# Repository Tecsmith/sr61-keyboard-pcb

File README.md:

# SR61 - MicroMod 60% Custom Keyboard PCB

[![CC-0 license](https://shields.io/badge/-BY--SA_4.0-black?logo=creativecommons&logoColor=%23000&labelColor=%23c1c1c1
)](https://creativecommons.org/licenses/by-sa/4.0/)

***Featuring SparkFun's MicroMod Processor Boards***

---

> [PCBWay](https://pcbway.com) had gratefully sponsored the production of the first 5 RevA PCBs, and a partial assembly service.
>
> 
>
> Thank you [PCBWay](https://pcbway.com/)!

Please follow the updates to this production process on the [changelog](CHANGELOG.md) page.

---

Published as Open Source, under a [ Creative Commons Share-alike 4.0 International](LICENSE.md).

### **Rev C** &nbsp; 

> ~~&#128077; **WORKING, OK TO BUILD**~~ &nbsp; 

* [PDF Schematic](docs/sr61-revC.pdf)
* [EAGLE PCB](EAGLE/sr61/sr61-revC.brd)
* [EAGLE Schematic](EAGLE/sr61/sr61-revC.sch)

* Notes:
    - Keymap Working on both STM32 and PR2040
    - *(Optional EEPROM not tested yet)*

### QMK code:

* https://github.com/Tecsmith/sr61-keyboard-qmk
* USB Identifier registered with [pid.codes](https://pid.codes/) = [`1209`/`7672`](https://pid.codes/1209/7672/)

### Layout

* [KLE JSON](./kle/sr61-micromod-poker.json)

*****

## Features

**SR61-MicroMod** - using SparkFun MicroMod STM32 or RP2040 M.2 module

### Core Design Elements

- 60% form factor
    - Design to be compatible with GH60/HK60 cases
    - Also compatible with Anne Pro 2 cases *(~~drop in~~ QMK replacement for existing AP2's or AP2 cases)* *[Removal of battery and minor case cut in the battery compartment required.]*
    - MicroMod positioned in case *"battery compartment"* space.

- QMK + VIA default f/w
    - Wired only *(no wireless)*
    - Default key-maps for Mac users

- User choice of microcontroller
    
    - [STM32 Processor](https://www.sparkfun.com/products/17713) 
        - ARM Cortex-M4, 168MHz, 1MB Flash, 192kB SRAM
        - https://github.com/Tecsmith/sr61-keyboard-qmk

    - [RP2040 Processor](https://www.sparkfun.com/products/17720) 
        - ARM Cortex-M0+, 133MHz, 128Mb Flash (16MB external), 264kB SRAM in six banks
        
- USB-C *(left side)*

    ... but also optional JST connector for [ai03 Unified C3 Daughterboard](https://github.com/ai03-2725/Unified-Daughterboard)

- ESD, Over Voltage and Over Current protection

    ... and cable shield noise filter

- Hot-swap, 5 pin switch slots

- PCB mounted stabs compatibility

- Dual ANSI / ISO layout support

- 61-Key (ANSI) / 62-Key (ISO) Layout [1.25, 1.25, 1.25, **6.25**, 1.25, 1.25, 1.25, 1.25] bottom row *(a.k.a. "Poker" / "POK3R" Layout)*

- Limited RGB LEDs *(SK6812 mini-E)*

    - RGB Caps Lock Indicator

    - North facing RGB's under the `5`, `6`, `7` & `8` keys for layer indicator

    - WS2812/SK6812 breakout for optional external LEDs

- Spare GPIO pins (`52` & `63`) breakout for expansion

   ... e.g., ~~add speaker~~

- Both `[Reset]` and `[Boot]` buttons *(as per MicroMod ref. design)*

    ... plus under space-bar Boot pins for bootload without disassembly *(press while inserting cable for bootloader function)*

---

Made with :heart: by Silvino R.

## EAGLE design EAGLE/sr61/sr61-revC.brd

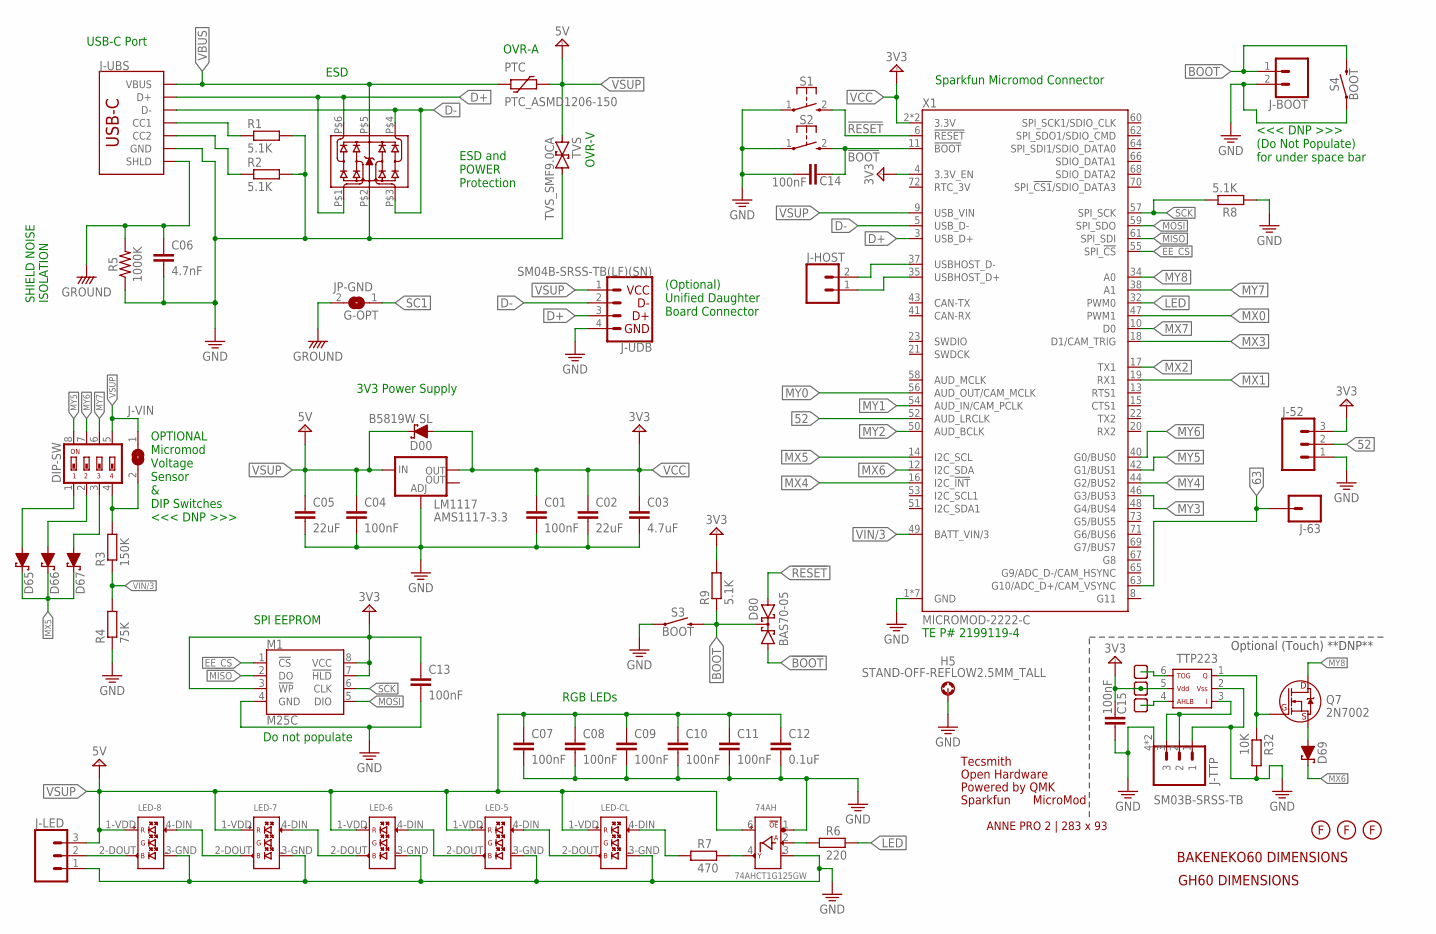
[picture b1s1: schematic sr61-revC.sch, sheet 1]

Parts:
74AH: 74AHCT1G125GW; SC-88A__TSSOP5__SOT353-1
C01, C04: 100nF; 0603
C02, C05: 22uF; 0603
C03: 4.7uF; 0603
C06: 4.7nF; 0603
C07, C08, C09, C10, C11, C13, C14, C15: 100nF; C0603
C12: 0.1uF; C0603
D00: B5819W SL; SOD-123
D65, D66, D67, D69: 1N5819WS; SOD-123
D80: BAS70-05; SOT23
DIP-SW: DIP004; DIP-1.27-004
ESD: ESD_SRV05-4; SOT-23-6L
FP_AP2: FOOTPRINT-AP2
H5: STAND-OFF-REFLOW2.5MM_TALL; STAND-OFF-REFLOW-M2.5
J-52: CONN_03; 1X03
J-63: CONN_01; 1X01
J-BOOT: CONN_02; 1X02
J-HOST: CONN_02; 1X02
J-LED: CONN_03; 1X03
J-TTP: SM03B-SRSS-TB; CONN_SM03B-SRSS-TB_JST
J-UBS: USB_C_2-LAYER; USB-C-16P
J-UDB: SM04B-SRSS-TB(LF)(SN); 1X04_1MM_RA
J-VIN: JUMPER-1X2; SOLDERJUMPER_ARROW_NOPASTE
JP-GND: G-OPT; SOLDERJUMPER_ARROW_NOPASTE
LED-5, LED-6, LED-7, LED-8: SK6812-E-REVERSE; SK6812-E-MILL
LED-CL: SK6812-E-REVERSE; SK6812-E-MILL
LM1117: AMS1117-3.3; SOT223
LOGO1: OSHW-LOGOL; OSHW-LOGO-L
M1: M25C; 8-SOIC
PTC: PTC_ASMD1206-150; SMD_PTC
Q7: 2N7002; SOT23-3
R1, R2, R8, R9: 5.1K; R0603
R3: 150K; R0603
R4: 75K; R0603
R5: 1000K; 0603
R6: 220; R0603
R7: 470; R0603
R32: 10K; R0603
S1, S2: MOMENTARY-SWITCH-SPST-1; SKRKAEE020
S3, S4: BOOT; TACTILE_SWITCH_SMD_5.2MM
TP1, TP2, TP3: TEST-POINT.3SQ; PAD.03X.03-SQ
TTP223: TTP223-BA6; TTP223B
TVS: TVS_SMF9.0CA; SOD123FL-BI
U$3: MICROMOD-LOGO
U$5: SPARKFUN_LOGO0.2; SFE_LOGO_NAME_FLAME_.2
U$6: QMK_LOGO
U$8: TECSMITH-LOGOLONG; TECSMITH-NAME
U$20, U$21, U$22: FIDUCIAL
U$24: FOOTPRINT-BAKENEKO60
U$27: FOOTPRINT-DIMS-GH60
X1: MICROMOD-2222-C; M.2-CONNECTOR-E

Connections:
52: J-52.2, X1.52 (AUD_LRCLK)
63: J-63.1, X1.63 (G10/ADC_D+/CAM_VSYNC)
!BOOT: C14.1, D80.1 (A1), S2.2 (3), X1.11 (!BOOT!)
!RESET: D80.2 (A2), S1.2 (3), X1.6 (!RESET!)
BOOT: D80.3 (C), J-BOOT.1, R9.1, S3.3 (2), S3.4 (2), S4.3 (2), S4.4 (2)
CC1: J-UBS.A5 (CC1), R1.1
CC2: J-UBS.B5 (CC2), R2.1
D+: ESD.P$1, ESD.P$6, J-UBS.A6 (D+), J-UBS.B6 (D+), J-UDB.3 (D+), X1.3 (USB_D+)
D-: ESD.P$3, ESD.P$4, J-UBS.A7 (D-), J-UBS.B7 (D-), J-UDB.2 (D-), X1.5 (USB_D-)
EE_CS: M1.1 (!CS), X1.55 (SPI_!CS!)
GND: 74AH.1 (!OE), 74AH.3 (3_GND), C01.2, C02.2, C03.2, C04.2, C05.2, C06.2, C07.2, C08.2, C09.2, C10.2, C11.2, C12.2, C13.2, C14.2, C15.2, ESD.P$2, H5.1, J-52.1, J-BOOT.2, J-LED.1, J-TTP.1, J-TTP.4 (M), J-TTP.5 (M), J-UBS.GND, J-UBS.GND2 (GND), J-UDB.4 (GND), LED-5.3-GND (3_GND), LED-6.3-GND (3_GND), LED-7.3-GND (3_GND), LED-8.3-GND (3_GND), LED-CL.3-GND (3_GND), LM1117.1 (ADJ), M1.4 (GND), R1.2, R2.2, R4.1, R5.1, R8.1, R32.2, S1.1, S2.1, S3.1, S3.2 (1), S4.1, S4.2 (1), TTP223.2, TVS.P$2 (2), X1.1 (GND), X1.7 (GND), X1.33 (GND), X1.36 (GND), X1.39 (GND), X1.45 (GND), X1.75 (GND)
GROUND: C06.1, J-UBS.SHLD1 (SHLD), J-UBS.SHLD2 (SHLD), J-UBS.SHLD3 (SHLD), J-UBS.SHLD4 (SHLD), J-UBS.SHLD5 (SHLD), J-UBS.SHLD6 (SHLD), J-UBS.SHLD7 (SHLD), J-UBS.SHLD8 (SHLD), JP-GND.2, R5.2
LED: R6.2, X1.32 (PWM0)
LED1ST: 74AH.2 (A_DIN), R6.1
MISO: M1.2 (DO), X1.61 (SPI_SDI)
MOSI: M1.5 (DIO), X1.59 (SPI_SDO)
MX0: X1.47 (PWM1); also elsewhere on the board
MX1: X1.19 (RX1); also elsewhere on the board
MX2: X1.17 (TX1); also elsewhere on the board
MX3: X1.18 (D1/CAM_TRIG); also elsewhere on the board
MX4: X1.16 (I2C_!INT!); also elsewhere on the board
MX5: D65.C, D66.C, D67.C, X1.14 (I2C_SCL); also elsewhere on the board
MX6: D69.C, X1.12 (I2C_SDA); also elsewhere on the board
MX7: X1.10 (D0); also elsewhere on the board
MY0: X1.56 (AUD_OUT/CAM_MCLK); also elsewhere on the board
MY1: X1.54 (AUD_IN/CAM_PCLK); also elsewhere on the board
MY2: X1.50 (AUD_BCLK); also elsewhere on the board
MY3: X1.46 (G3/BUS3); also elsewhere on the board
MY4: X1.44 (G2/BUS2); also elsewhere on the board
MY5: DIP-SW.8, X1.42 (G1/BUS1); also elsewhere on the board
MY6: DIP-SW.7, X1.40 (G0/BUS0); also elsewhere on the board
MY7: DIP-SW.6, X1.38 (A1); also elsewhere on the board
MY8: Q7.3 (D), X1.34 (A0); also elsewhere on the board
unnamed: LED-5.4-DIN (4_DIN), LED-CL.2-DOUT (2_DOUT)
unnamed: LED-5.2-DOUT (2_DOUT), LED-6.4-DIN (4_DIN)
unnamed: LED-6.2-DOUT (2_DOUT), LED-7.4-DIN (4_DIN)
unnamed: LED-7.2-DOUT (2_DOUT), LED-8.4-DIN (4_DIN)
unnamed: 74AH.4 (Y_DOUT), R7.2
unnamed: LED-CL.4-DIN (4_DIN), R7.1
unnamed: TP1.1, TTP223.6
unnamed: J-LED.2, LED-8.2-DOUT (2_DOUT)
unnamed: D65.A, DIP-SW.1
unnamed: DIP-SW.4, J-VIN.2, R3.2
unnamed: D66.A, DIP-SW.2
unnamed: D67.A, DIP-SW.3
unnamed: TP3.1, TTP223.4
unnamed: D69.A, Q7.2 (S)
unnamed: Q7.1 (G), R32.1, TTP223.1
unnamed: J-TTP.2, J-TTP.3, TTP223.3
SC1: JP-GND.1
SCK: M1.6 (CLK), R8.2, X1.57 (SPI_SCK)
USBHOST_D+: J-HOST.1, X1.35 (USBHOST_D+)
USBHOST_D-: J-HOST.2, X1.37 (USBHOST_D-)
VBUS: ESD.P$5, J-UBS.VBUS1 (VBUS), J-UBS.VBUS2 (VBUS), PTC.P$1 (1)
VCC: C01.1, C02.1, C03.1, C13.1, C15.1, D00.A, J-52.3, LM1117.2 (OUT), M1.3 (!WP), M1.7 (!HLD), M1.8 (VCC), R9.2, TP2.1, TTP223.5, X1.2 (3.3V), X1.4 (3.3V_EN), X1.74 (3.3V)
VIN/3: R3.1, R4.2, X1.49 (BATT_VIN/3)
VSUP: 74AH.6 (5_VCC), C04.1, C05.1, C07.1, C08.1, C09.1, C10.1, C11.1, C12.1, D00.C, DIP-SW.5, J-LED.3, J-UDB.1 (VCC), J-VIN.1, LED-5.1-VDD (1_VDD), LED-6.1-VDD (1_VDD), LED-7.1-VDD (1_VDD), LED-8.1-VDD (1_VDD), LED-CL.1-VDD (1_VDD), LM1117.3 (IN), PTC.P$2 (2), TVS.P$1 (1), X1.9 (USB_VIN)

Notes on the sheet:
ESD
OVR-A
OVR-V
USB-C Port
ESD and POWER Protection
OPTIONAL Micromod Voltage Sensor & DIP Switches <<< DNP >>>
(Optional) Unified Daughter Board Connector
Sparkfun Micromod Connector
3V3 Power Supply
RGB LEDs
SHIELD NOISE ISOLATION
SPI EEPROM
TE P# 2199119-4
<<< DNP >>> (Do Not Populate) for under space bar
Do not populate
Optional (Touch) **DNP**

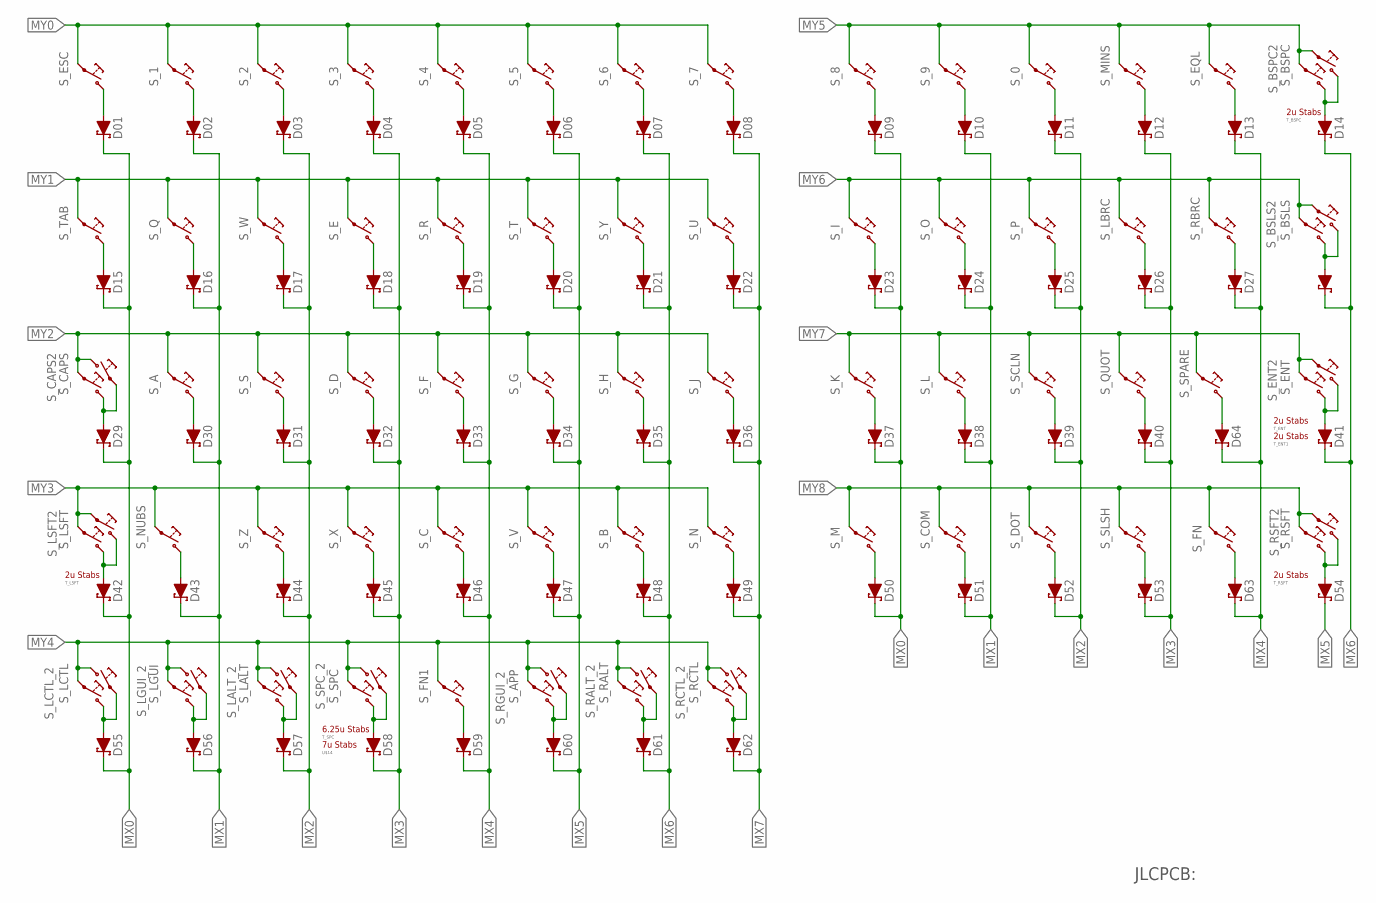
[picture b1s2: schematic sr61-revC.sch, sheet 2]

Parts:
D01, D02, D03, D04, D05, D06, D07, D08, D09, D10, D11, D12, D13, D14, D15, D16, D17, D18, D19, D20, D21, D22, D23, D24, D25, D26, D27, D28, D29, D30, D31, D32, D33, D34, D35, D36, D37, D38, D39, D40, D41, D42, D43, D44, D45, D46, D47, D48, D49, D50, D51, D52, D53, D54, D55, D56, D57, D58, D59, D60, D61, D62, D63, D64: 1N5819WS; SOD-123
S_0, S_1, S_2, S_3, S_4, S_5, S_6, S_7, S_8, S_9: MX-5-PIN-HOTSWAP-VIA
S_A: MX-5-PIN-HOTSWAP-VIA
S_APP: MX-5-PIN-HOTSWAP-VIA
S_B: MX-5-PIN-HOTSWAP-VIA
S_BSLS: MX-5-PIN-HOTSWAP-VIA
S_BSLS2: MX-5-PIN-HOTSWAP-VIANO-SILK; MX-5-PIN-HOTSWAP-VIA-NS
S_BSPC: MX-5-PIN-HOTSWAP-VIA
S_BSPC2: MX-5-PIN-HOTSWAP-VIANO-SILK; MX-5-PIN-HOTSWAP-VIA-NS
S_C: MX-5-PIN-HOTSWAP-VIA
S_CAPS: MX-5-PIN-HOTSWAP-VIA
S_CAPS2: MX-5-PIN-MILMAX-3305-XNO-SILK; MX-5-PIN-MILMAX-3305-X-NS
S_COM: MX-5-PIN-HOTSWAP-VIA
S_D: MX-5-PIN-HOTSWAP-VIA
S_DOT: MX-5-PIN-HOTSWAP-VIA
S_E: MX-5-PIN-HOTSWAP-VIA
S_ENT: MX-5-PIN-HOTSWAP-VIA
S_ENT2: MX-5-PIN-HOTSWAP-VIANO-SILK; MX-5-PIN-HOTSWAP-VIA-NS
S_EQL: MX-5-PIN-HOTSWAP-VIA
S_ESC: MX-5-PIN-HOTSWAP-VIA
S_F: MX-5-PIN-HOTSWAP-VIA
S_FN: MX-5-PIN-HOTSWAP-VIANO-SILK; MX-5-PIN-HOTSWAP-VIA-NS
S_FN1: MX-5-PIN-HOTSWAP-VIA
S_G: MX-5-PIN-HOTSWAP-VIA
S_H: MX-5-PIN-HOTSWAP-VIA
S_I: MX-5-PIN-HOTSWAP-VIA
S_J: MX-5-PIN-HOTSWAP-VIA
S_K: MX-5-PIN-HOTSWAP-VIA
S_L: MX-5-PIN-HOTSWAP-VIA
S_LALT: MX-5-PIN-HOTSWAP-VIA
S_LALT_2: MX-5-PIN-HOTSWAP-VIANO-SILK; MX-5-PIN-HOTSWAP-VIA-NS
S_LBRC: MX-5-PIN-HOTSWAP-VIA
S_LCTL: MX-5-PIN-HOTSWAP-VIA
S_LCTL_2: MX-5-PIN-HOTSWAP-VIANO-SILK; MX-5-PIN-HOTSWAP-VIA-NS
S_LGUI: MX-5-PIN-HOTSWAP-VIA
S_LGUI_2: MX-5-PIN-HOTSWAP-VIANO-SILK; MX-5-PIN-HOTSWAP-VIA-NS
S_LSFT: MX-5-PIN-HOTSWAP-VIA
S_LSFT2: MX-5-PIN-HOTSWAP-VIANO-SILK; MX-5-PIN-HOTSWAP-VIA-NS
S_M: MX-5-PIN-HOTSWAP-VIA
S_MINS: MX-5-PIN-HOTSWAP-VIA
S_N: MX-5-PIN-HOTSWAP-VIA
S_NUBS: MX-5-PIN-HOTSWAP-VIANO-SILK; MX-5-PIN-HOTSWAP-VIA-NS
S_O: MX-5-PIN-HOTSWAP-VIA
S_P: MX-5-PIN-HOTSWAP-VIA
S_Q: MX-5-PIN-HOTSWAP-VIA
S_QUOT: MX-5-PIN-HOTSWAP-VIA
S_R: MX-5-PIN-HOTSWAP-VIA
S_RALT: MX-5-PIN-HOTSWAP-VIA
S_RALT_2: MX-5-PIN-HOTSWAP-VIANO-SILK; MX-5-PIN-HOTSWAP-VIA-NS
S_RBRC: MX-5-PIN-HOTSWAP-VIA
S_RCTL: MX-5-PIN-HOTSWAP-VIA
S_RCTL_2: MX-5-PIN-HOTSWAP-VIANO-SILK; MX-5-PIN-HOTSWAP-VIA-NS
S_RGUI_2: MX-5-PIN-HOTSWAP-VIANO-SILK; MX-5-PIN-HOTSWAP-VIA-NS
S_RSFT: MX-5-PIN-HOTSWAP-VIA
S_RSFT2: MX-5-PIN-HOTSWAP-VIANO-SILK; MX-5-PIN-HOTSWAP-VIA-NS
S_S: MX-5-PIN-HOTSWAP-VIA
S_SCLN: MX-5-PIN-HOTSWAP-VIA
S_SLSH: MX-5-PIN-HOTSWAP-VIA
S_SPARE: MX-5-PIN-HOTSWAP-VIANO-SILK; MX-5-PIN-HOTSWAP-VIA-NS
S_SPC: MX-5-PIN-HOTSWAP-VIA
S_SPC_2: MX-5-PIN-HOTSWAP-VIANO-SILK; MX-5-PIN-HOTSWAP-VIA-NS
S_T: MX-5-PIN-HOTSWAP-VIA
S_TAB: MX-5-PIN-HOTSWAP-VIA
S_U: MX-5-PIN-HOTSWAP-VIA
S_V: MX-5-PIN-HOTSWAP-VIA
S_W: MX-5-PIN-HOTSWAP-VIA
S_X: MX-5-PIN-HOTSWAP-VIA
S_Y: MX-5-PIN-HOTSWAP-VIA
S_Z: MX-5-PIN-HOTSWAP-VIA
T_BSPC: MX-STABS-200U
T_ENT, T_ENT1: MX-STABS-200U
T_LSFT: MX-STABS-200U
T_RSFT: MX-STABS-200U
T_SPC: MX-STABS-625U
U$14: MX-STABS-700U
U$26: ?; JLC_ORDER_NUMBER_QR_5X5

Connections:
MX0: D01.C, D09.C, D15.C, D23.C, D29.C, D37.C, D42.C, D50.C, D55.C; also elsewhere on the board
MX1: D02.C, D10.C, D16.C, D24.C, D30.C, D38.C, D43.C, D51.C, D56.C; also elsewhere on the board
MX2: D03.C, D11.C, D17.C, D25.C, D31.C, D39.C, D44.C, D52.C, D57.C; also elsewhere on the board
MX3: D04.C, D12.C, D18.C, D26.C, D32.C, D40.C, D45.C, D53.C, D58.C; also elsewhere on the board
MX4: D05.C, D13.C, D19.C, D27.C, D33.C, D46.C, D59.C, D63.C, D64.C; also elsewhere on the board
MX5: D06.C, D20.C, D34.C, D47.C, D54.C, D60.C; also elsewhere on the board
MX6: D07.C, D14.C, D21.C, D28.C, D35.C, D41.C, D48.C, D61.C; also elsewhere on the board
MX7: D08.C, D22.C, D36.C, D49.C, D62.C; also elsewhere on the board
MY0: S_1.2@1 (1), S_1.2@2 (1), S_2.2@1 (1), S_2.2@2 (1), S_3.2@1 (1), S_3.2@2 (1), S_4.2@1 (1), S_4.2@2 (1), S_5.2@1 (1), S_5.2@2 (1), S_6.2@1 (1), S_6.2@2 (1), S_7.2@1 (1), S_7.2@2 (1), S_ESC.2@1 (1), S_ESC.2@2 (1); also elsewhere on the board
MY1: S_E.2@1 (1), S_E.2@2 (1), S_Q.2@1 (1), S_Q.2@2 (1), S_R.2@1 (1), S_R.2@2 (1), S_T.2@1 (1), S_T.2@2 (1), S_TAB.2@1 (1), S_TAB.2@2 (1), S_U.2@1 (1), S_U.2@2 (1), S_W.2@1 (1), S_W.2@2 (1), S_Y.2@1 (1), S_Y.2@2 (1); also elsewhere on the board
MY2: S_A.2@1 (1), S_A.2@2 (1), S_CAPS.2@1 (1), S_CAPS.2@2 (1), S_CAPS2.1 (2), S_D.2@1 (1), S_D.2@2 (1), S_F.2@1 (1), S_F.2@2 (1), S_G.2@1 (1), S_G.2@2 (1), S_H.2@1 (1), S_H.2@2 (1), S_J.2@1 (1), S_J.2@2 (1), S_S.2@1 (1), S_S.2@2 (1); also elsewhere on the board
MY3: S_B.2@1 (1), S_B.2@2 (1), S_C.2@1 (1), S_C.2@2 (1), S_LSFT.2@1 (1), S_LSFT.2@2 (1), S_LSFT2.2@1 (1), S_LSFT2.2@2 (1), S_N.2@1 (1), S_N.2@2 (1), S_NUBS.2@1 (1), S_NUBS.2@2 (1), S_V.2@1 (1), S_V.2@2 (1), S_X.2@1 (1), S_X.2@2 (1), S_Z.2@1 (1), S_Z.2@2 (1); also elsewhere on the board
MY4: S_APP.2@1 (1), S_APP.2@2 (1), S_FN1.2@1 (1), S_FN1.2@2 (1), S_LALT.2@1 (1), S_LALT.2@2 (1), S_LALT_2.1@1 (2), S_LALT_2.1@2 (2), S_LCTL.2@1 (1), S_LCTL.2@2 (1), S_LCTL_2.1@1 (2), S_LCTL_2.1@2 (2), S_LGUI.2@1 (1), S_LGUI.2@2 (1), S_LGUI_2.1@1 (2), S_LGUI_2.1@2 (2), S_RALT.2@1 (1), S_RALT.2@2 (1), S_RALT_2.1@1 (2), S_RALT_2.1@2 (2), S_RCTL.2@1 (1), S_RCTL.2@2 (1), S_RCTL_2.1@1 (2), S_RCTL_2.1@2 (2), S_RGUI_2.1@1 (2), S_RGUI_2.1@2 (2), S_SPC.2@1 (1), S_SPC.2@2 (1), S_SPC_2.1@1 (2), S_SPC_2.1@2 (2); also elsewhere on the board
MY5: S_0.2@1 (1), S_0.2@2 (1), S_8.2@1 (1), S_8.2@2 (1), S_9.2@1 (1), S_9.2@2 (1), S_BSPC.2@1 (1), S_BSPC.2@2 (1), S_BSPC2.2@1 (1), S_BSPC2.2@2 (1), S_EQL.2@1 (1), S_EQL.2@2 (1), S_MINS.2@1 (1), S_MINS.2@2 (1); also elsewhere on the board
MY6: S_BSLS.2@1 (1), S_BSLS.2@2 (1), S_BSLS2.2@1 (1), S_BSLS2.2@2 (1), S_I.2@1 (1), S_I.2@2 (1), S_LBRC.2@1 (1), S_LBRC.2@2 (1), S_O.2@1 (1), S_O.2@2 (1), S_P.2@1 (1), S_P.2@2 (1), S_RBRC.2@1 (1), S_RBRC.2@2 (1); also elsewhere on the board
MY7: S_ENT.2@1 (1), S_ENT.2@2 (1), S_ENT2.2@1 (1), S_ENT2.2@2 (1), S_K.2@1 (1), S_K.2@2 (1), S_L.2@1 (1), S_L.2@2 (1), S_QUOT.2@1 (1), S_QUOT.2@2 (1), S_SCLN.2@1 (1), S_SCLN.2@2 (1), S_SPARE.2@1 (1), S_SPARE.2@2 (1); also elsewhere on the board
MY8: S_COM.2@1 (1), S_COM.2@2 (1), S_DOT.2@1 (1), S_DOT.2@2 (1), S_FN.2@1 (1), S_FN.2@2 (1), S_M.2@1 (1), S_M.2@2 (1), S_RSFT.2@1 (1), S_RSFT.2@2 (1), S_RSFT2.2@1 (1), S_RSFT2.2@2 (1), S_SLSH.2@1 (1), S_SLSH.2@2 (1); also elsewhere on the board
unnamed: D01.A, S_ESC.1@1 (2), S_ESC.1@2 (2)
unnamed: D02.A, S_1.1@1 (2), S_1.1@2 (2)
unnamed: D03.A, S_2.1@1 (2), S_2.1@2 (2)
unnamed: D04.A, S_3.1@1 (2), S_3.1@2 (2)
unnamed: D05.A, S_4.1@1 (2), S_4.1@2 (2)
unnamed: D06.A, S_5.1@1 (2), S_5.1@2 (2)
unnamed: D07.A, S_6.1@1 (2), S_6.1@2 (2)
unnamed: D08.A, S_7.1@1 (2), S_7.1@2 (2)
unnamed: D09.A, S_8.1@1 (2), S_8.1@2 (2)
unnamed: D10.A, S_9.1@1 (2), S_9.1@2 (2)
unnamed: D11.A, S_0.1@1 (2), S_0.1@2 (2)
unnamed: D12.A, S_MINS.1@1 (2), S_MINS.1@2 (2)
unnamed: D13.A, S_EQL.1@1 (2), S_EQL.1@2 (2)
unnamed: D14.A, S_BSPC.1@1 (2), S_BSPC.1@2 (2), S_BSPC2.1@1 (2), S_BSPC2.1@2 (2)
unnamed: D15.A, S_TAB.1@1 (2), S_TAB.1@2 (2)
unnamed: D16.A, S_Q.1@1 (2), S_Q.1@2 (2)
unnamed: D17.A, S_W.1@1 (2), S_W.1@2 (2)
unnamed: D18.A, S_E.1@1 (2), S_E.1@2 (2)
unnamed: D19.A, S_R.1@1 (2), S_R.1@2 (2)
unnamed: D20.A, S_T.1@1 (2), S_T.1@2 (2)
unnamed: D21.A, S_Y.1@1 (2), S_Y.1@2 (2)
unnamed: D22.A, S_U.1@1 (2), S_U.1@2 (2)
unnamed: D23.A, S_I.1@1 (2), S_I.1@2 (2)
unnamed: D24.A, S_O.1@1 (2), S_O.1@2 (2)
unnamed: D25.A, S_P.1@1 (2), S_P.1@2 (2)
unnamed: D26.A, S_LBRC.1@1 (2), S_LBRC.1@2 (2)
unnamed: D27.A, S_RBRC.1@1 (2), S_RBRC.1@2 (2)
unnamed: D28.A, S_BSLS.1@1 (2), S_BSLS.1@2 (2), S_BSLS2.1@1 (2), S_BSLS2.1@2 (2)
unnamed: D30.A, S_A.1@1 (2), S_A.1@2 (2)
unnamed: D31.A, S_S.1@1 (2), S_S.1@2 (2)
unnamed: D32.A, S_D.1@1 (2), S_D.1@2 (2)
unnamed: D33.A, S_F.1@1 (2), S_F.1@2 (2)
unnamed: D34.A, S_G.1@1 (2), S_G.1@2 (2)
unnamed: D35.A, S_H.1@1 (2), S_H.1@2 (2)
unnamed: D36.A, S_J.1@1 (2), S_J.1@2 (2)
unnamed: D37.A, S_K.1@1 (2), S_K.1@2 (2)
unnamed: D38.A, S_L.1@1 (2), S_L.1@2 (2)
unnamed: D39.A, S_SCLN.1@1 (2), S_SCLN.1@2 (2)
unnamed: D40.A, S_QUOT.1@1 (2), S_QUOT.1@2 (2)
unnamed: D41.A, S_ENT.1@1 (2), S_ENT.1@2 (2), S_ENT2.1@1 (2), S_ENT2.1@2 (2)
unnamed: D42.A, S_LSFT.1@1 (2), S_LSFT.1@2 (2), S_LSFT2.1@1 (2), S_LSFT2.1@2 (2)
unnamed: D44.A, S_Z.1@1 (2), S_Z.1@2 (2)
unnamed: D45.A, S_X.1@1 (2), S_X.1@2 (2)
unnamed: D46.A, S_C.1@1 (2), S_C.1@2 (2)
unnamed: D47.A, S_V.1@1 (2), S_V.1@2 (2)
unnamed: D48.A, S_B.1@1 (2), S_B.1@2 (2)
unnamed: D49.A, S_N.1@1 (2), S_N.1@2 (2)
unnamed: D50.A, S_M.1@1 (2), S_M.1@2 (2)
unnamed: D51.A, S_COM.1@1 (2), S_COM.1@2 (2)
unnamed: D52.A, S_DOT.1@1 (2), S_DOT.1@2 (2)
unnamed: D53.A, S_SLSH.1@1 (2), S_SLSH.1@2 (2)
unnamed: D54.A, S_RSFT.1@1 (2), S_RSFT.1@2 (2), S_RSFT2.1@1 (2), S_RSFT2.1@2 (2)
unnamed: D55.A, S_LCTL.1@1 (2), S_LCTL.1@2 (2), S_LCTL_2.2@1 (1), S_LCTL_2.2@2 (1)
unnamed: D56.A, S_LGUI.1@1 (2), S_LGUI.1@2 (2), S_LGUI_2.2@1 (1), S_LGUI_2.2@2 (1)
unnamed: D57.A, S_LALT.1@1 (2), S_LALT.1@2 (2), S_LALT_2.2@1 (1), S_LALT_2.2@2 (1)
unnamed: D58.A, S_SPC.1@1 (2), S_SPC.1@2 (2), S_SPC_2.2@1 (1), S_SPC_2.2@2 (1)
unnamed: D59.A, S_FN1.1@1 (2), S_FN1.1@2 (2)
unnamed: D60.A, S_APP.1@1 (2), S_APP.1@2 (2), S_RGUI_2.2@1 (1), S_RGUI_2.2@2 (1)
unnamed: D61.A, S_RALT.1@1 (2), S_RALT.1@2 (2), S_RALT_2.2@1 (1), S_RALT_2.2@2 (1)
unnamed: D62.A, S_RCTL.1@1 (2), S_RCTL.1@2 (2), S_RCTL_2.2@1 (1), S_RCTL_2.2@2 (1)
unnamed: D29.A, S_CAPS.1@1 (2), S_CAPS.1@2 (2), S_CAPS2.2 (1)
unnamed: D43.A, S_NUBS.1@1 (2), S_NUBS.1@2 (2)
unnamed: D64.A, S_SPARE.1@1 (2), S_SPARE.1@2 (2)
unnamed: D63.A, S_FN.1@1 (2), S_FN.1@2 (2)

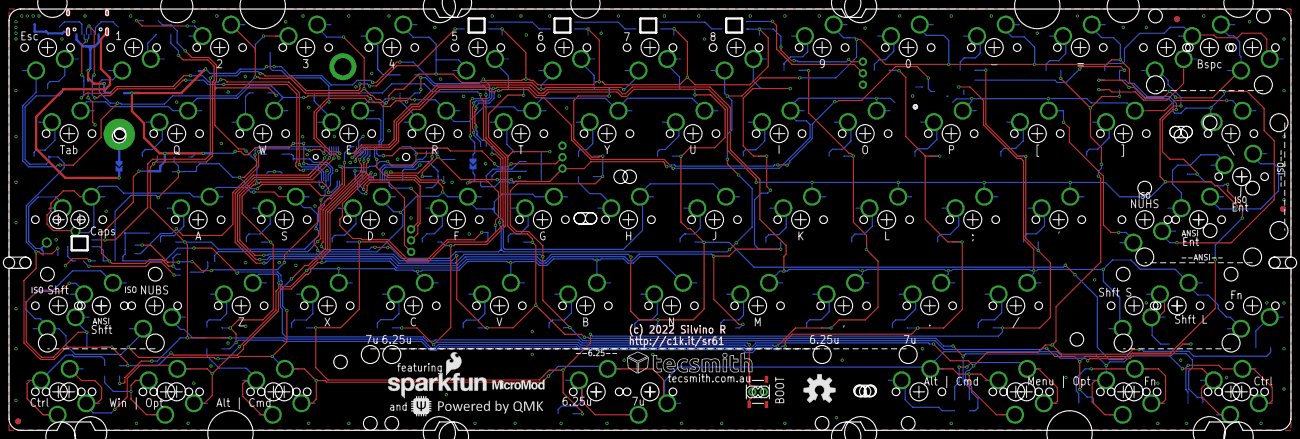
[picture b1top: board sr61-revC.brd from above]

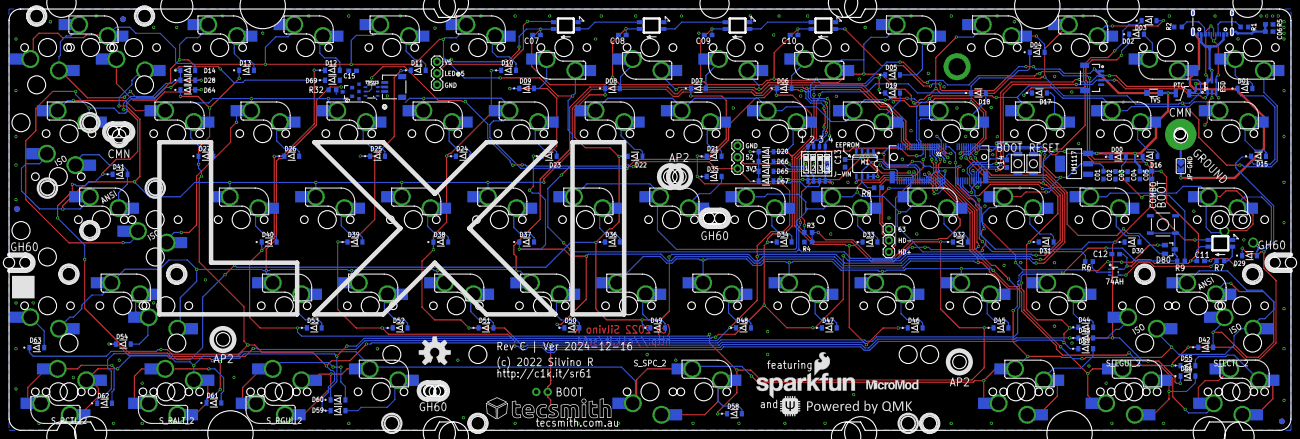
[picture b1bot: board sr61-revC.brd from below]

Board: 2 copper layers, 283.4 x 92.9 mm, 229 parts (126 on the bottom side), 120 nets.

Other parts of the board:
LOGO2: OSHW-LOGOL; OSHW-LOGO-L
U$7: TECSMITH-LOGOLONG; TECSMITH-NAME
U$10: SPARKFUN_LOGO0.2; SFE_LOGO_NAME_FLAME_.2
U$12: QMK_LOGO
U$13: MICROMOD-LOGO

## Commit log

2025-05-19 upgrades
2025-11-21 Retired

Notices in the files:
EAGLE/sr61/sr61-revC.brd:
(c) 2022 Silvino R
parts and their libraries:
SparkFun-Hardware: Licensing: Creative Commons ShareAlike 4.0 International - https://creativecommons.org/licenses/by-sa/4.0
